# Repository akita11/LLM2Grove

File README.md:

# LLM2Grove

M5Stack社の[LLM Module](https://www.switch-science.com/products/10334)を、Groveコネクタ経由で使用できるようにするためのボードです。LLM Moduleにとりつけ、GroveケーブルでM5StackシリーズのPortCに接続して使用します。（オプションでI2C通信を行うためのPortA用コネクタを実装できるパターンを用意してあります）（※LLM Moduleのファームウエア書き換えやLAN接続を行うことはできません）

## 使い方（接続方法）

M5Stack社の[LLM Module](https://www.switch-science.com/products/10334)に本ボードをとりつけます（両者のどちらが上側でも構いません）

Groveコネクタ（PortC用）をM5Stackシリーズ等のマイコンのGroveポートに接続して、UIFlowやその他のLLM Module用のソフトウエアで使用します。

M5Stackシリーズの場合はPortCに接続すると、直接LLM Moduleをスタック接続した場合と同等に扱うことができます。その他のPortに接続する場合は、それに応じた通信(UARTのTXとRX)用のピンを使用してください。

## Author

Junichi Akita (@akita11) / akita@ifdl.jp

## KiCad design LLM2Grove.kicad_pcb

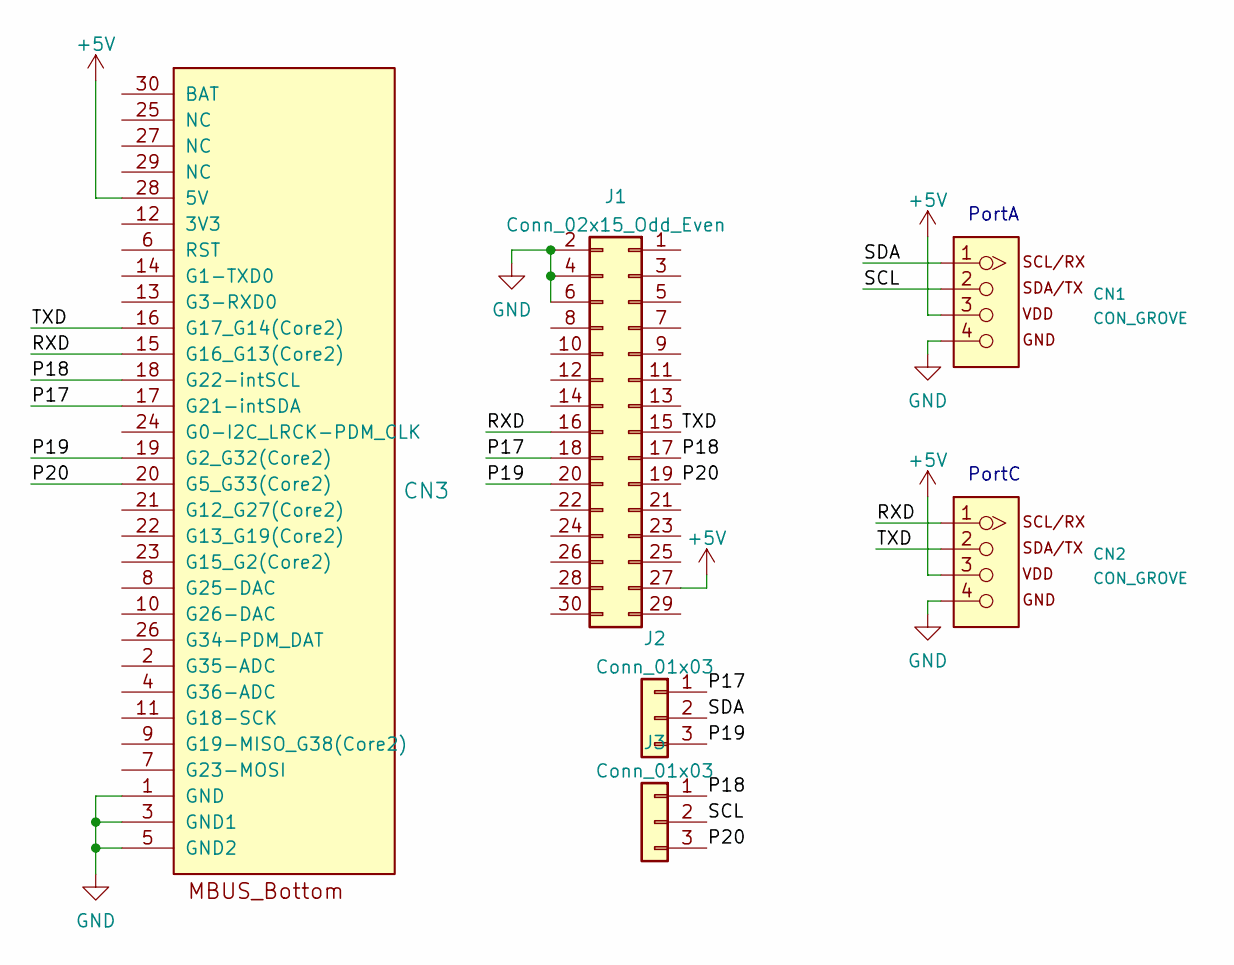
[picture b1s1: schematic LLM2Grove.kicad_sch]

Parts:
CN1, CN2: CON_GROVE; CON_GROVE_H_roundPad
CN3: CON_MBUS_bottom_Core2; M5STACK_BUS_30P
J1: Conn_02x15_Odd_Even; PinHeader_2x15_P2.54mm_Vertical
J2, J3: Conn_01x03; PinHeader_1x03_P2.54mm_Horizontal

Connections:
+5V: CN1.3, CN2.3, CN3.28 (5V), J1.27
/P17: CN3.17 (G21-intSDA), J1.18, J2.1
/P18: CN3.18 (G22-intSCL), J1.17, J3.1
/P19: CN3.19 (G2_G32(Core2)), J1.20, J2.3
/P20: CN3.20 (G5_G33(Core2)), J1.19, J3.3
/RXD: CN2.1, CN3.15 (G16_G13(Core2)), J1.16
/SCL: CN1.2, J3.2
/SDA: CN1.1, J2.2
/TXD: CN2.2, CN3.16 (G17_G14(Core2)), J1.15
GND: CN1.4, CN2.4, CN3.1 (GND), CN3.3 (GND1), CN3.5 (GND2), J1.2, J1.4, J1.6

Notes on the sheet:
PortA
PortC

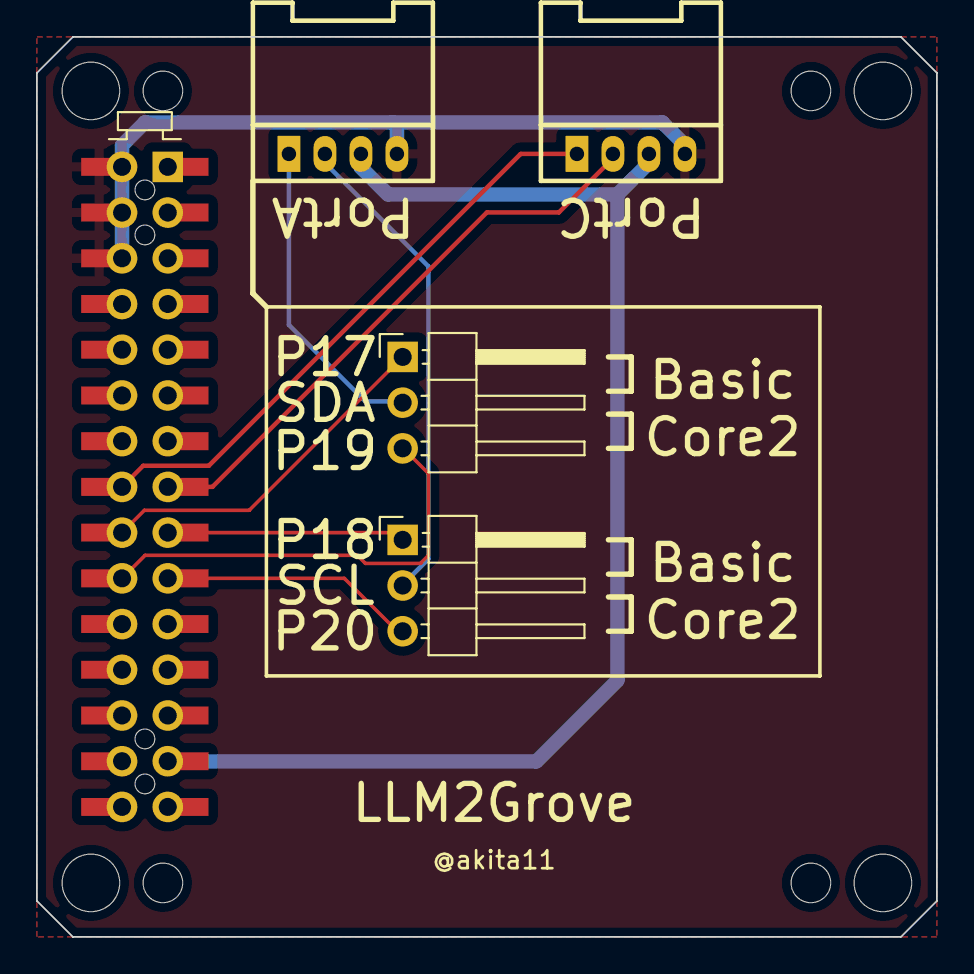
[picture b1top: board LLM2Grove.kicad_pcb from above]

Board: 2 copper layers, 50.0 x 50.0 mm, 6 parts (1 on the bottom side), 10 nets.
